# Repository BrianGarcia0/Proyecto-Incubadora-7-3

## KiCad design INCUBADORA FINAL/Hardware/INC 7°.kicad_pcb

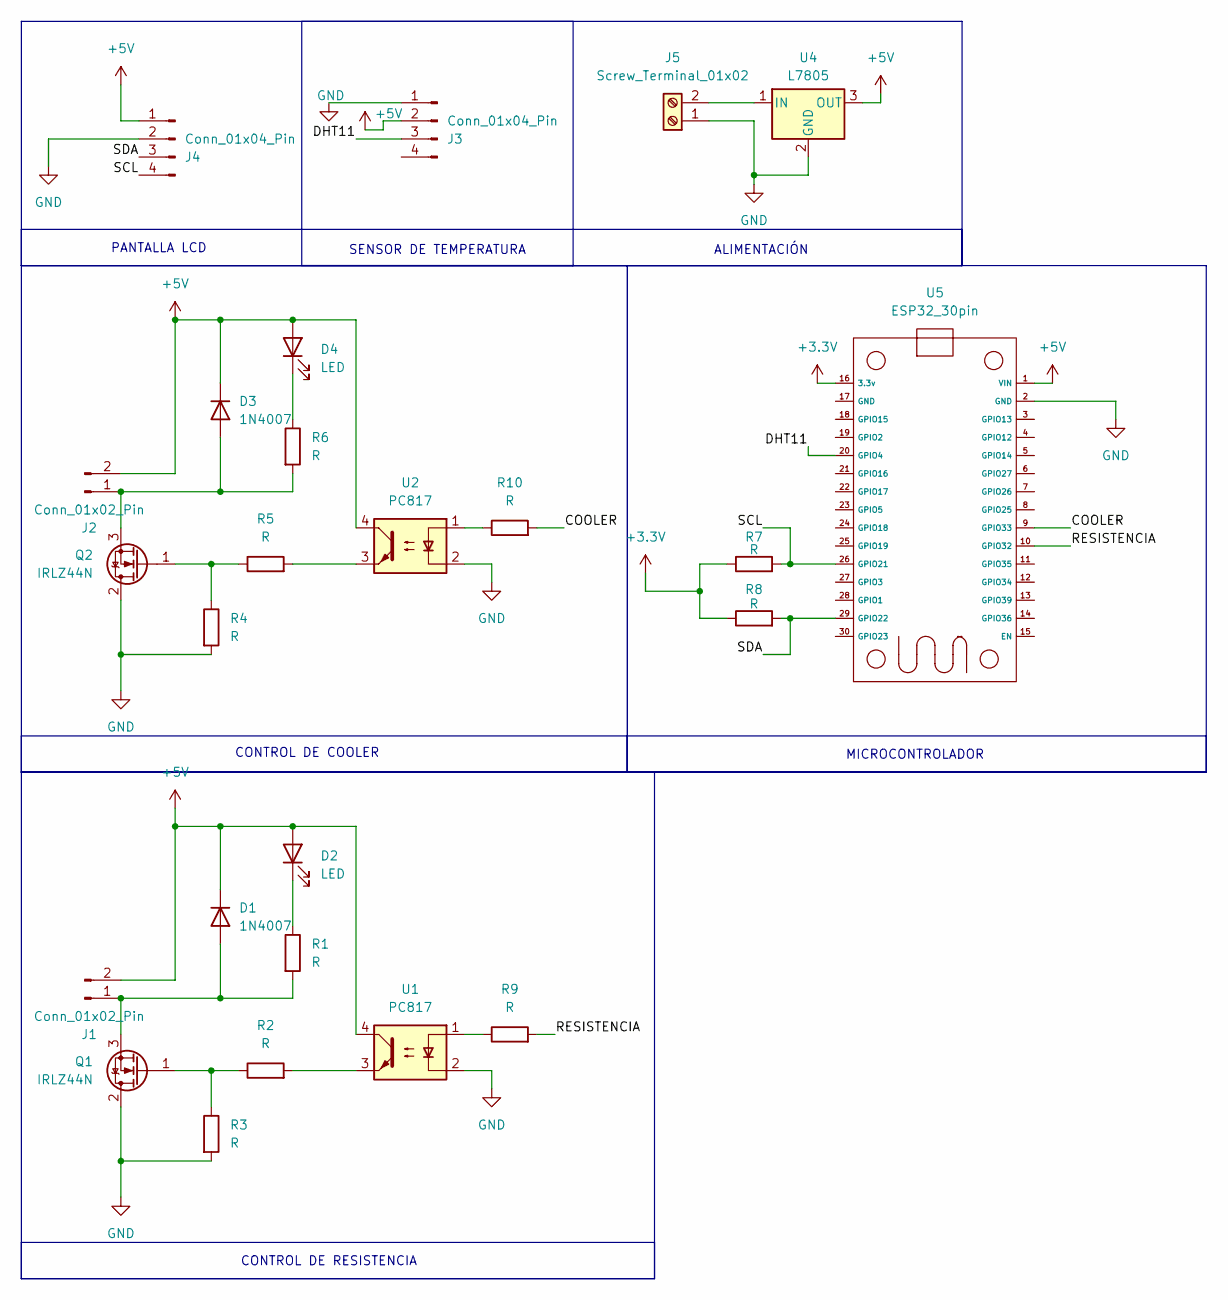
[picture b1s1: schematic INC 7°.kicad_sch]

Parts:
D1, D3: 1N4007; D_SMA
D2, D4: LED; LED_D3.0mm
J1, J2: Conn_01x02_Pin; PinSocket_1x02_P2.54mm_Vertical
J3, J4: Conn_01x04_Pin; PinSocket_1x04_P2.54mm_Vertical
J5: Screw_Terminal_01x02; TerminalBlock_MaiXu_MX126-5.0-02P_1x02_P5.00mm
Q1, Q2: IRLZ44N; TO-220-3_Vertical
R1, R2, R3, R4, R5, R6, R7, R8, R9, R10: R; R_0805_2012Metric
U1, U2: PC817; DIP-4_W7.62mm
U4: L7805; TO-220-3_Vertical
U5: ESP32_30pin

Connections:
+3.3V: R7.1, R8.1, U5.16 (3.3v)
+5V: D1.1 (K), D2.2 (A), D3.1 (K), D4.2 (A), J1.2, J2.2, J3.2, J4.1, U1.4, U2.4, U4.3 (OUT), U5.1 (VIN)
/COOLER: R10.2, U5.9 (GPIO33)
/DHT11: J3.3, U5.20 (GPIO4)
/RESISTENCIA: R9.2, U5.10 (GPIO32)
/SCL: J4.4, R7.2, U5.26 (GPIO21)
/SDA: J4.3, R8.2, U5.29 (GPIO22)
GND: J3.1, J4.2, J5.1, Q1.2 (D), Q2.2 (D), R3.2, R4.2, U1.2, U2.2, U4.2 (GND), U5.2 (GND)
unnamed: D1.2 (A), J1.1, Q1.3 (S), R1.2
unnamed: D2.1 (K), R1.1
unnamed: D3.2 (A), J2.1, Q2.3 (S), R6.2
unnamed: D4.1 (K), R6.1
unnamed: J5.2, U4.1 (IN)
unnamed: Q1.1 (G), R2.1, R3.1
unnamed: Q2.1 (G), R4.1, R5.1
unnamed: R2.2, U1.3
unnamed: R5.2, U2.3
unnamed: R9.1, U1.1
unnamed: R10.1, U2.1

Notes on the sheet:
CONTROL DE RESISTENCIA
PANTALLA LCD
MICROCONTROLADOR
CONTROL DE COOLER
SENSOR DE TEMPERATURA
ALIMENTACIÓN

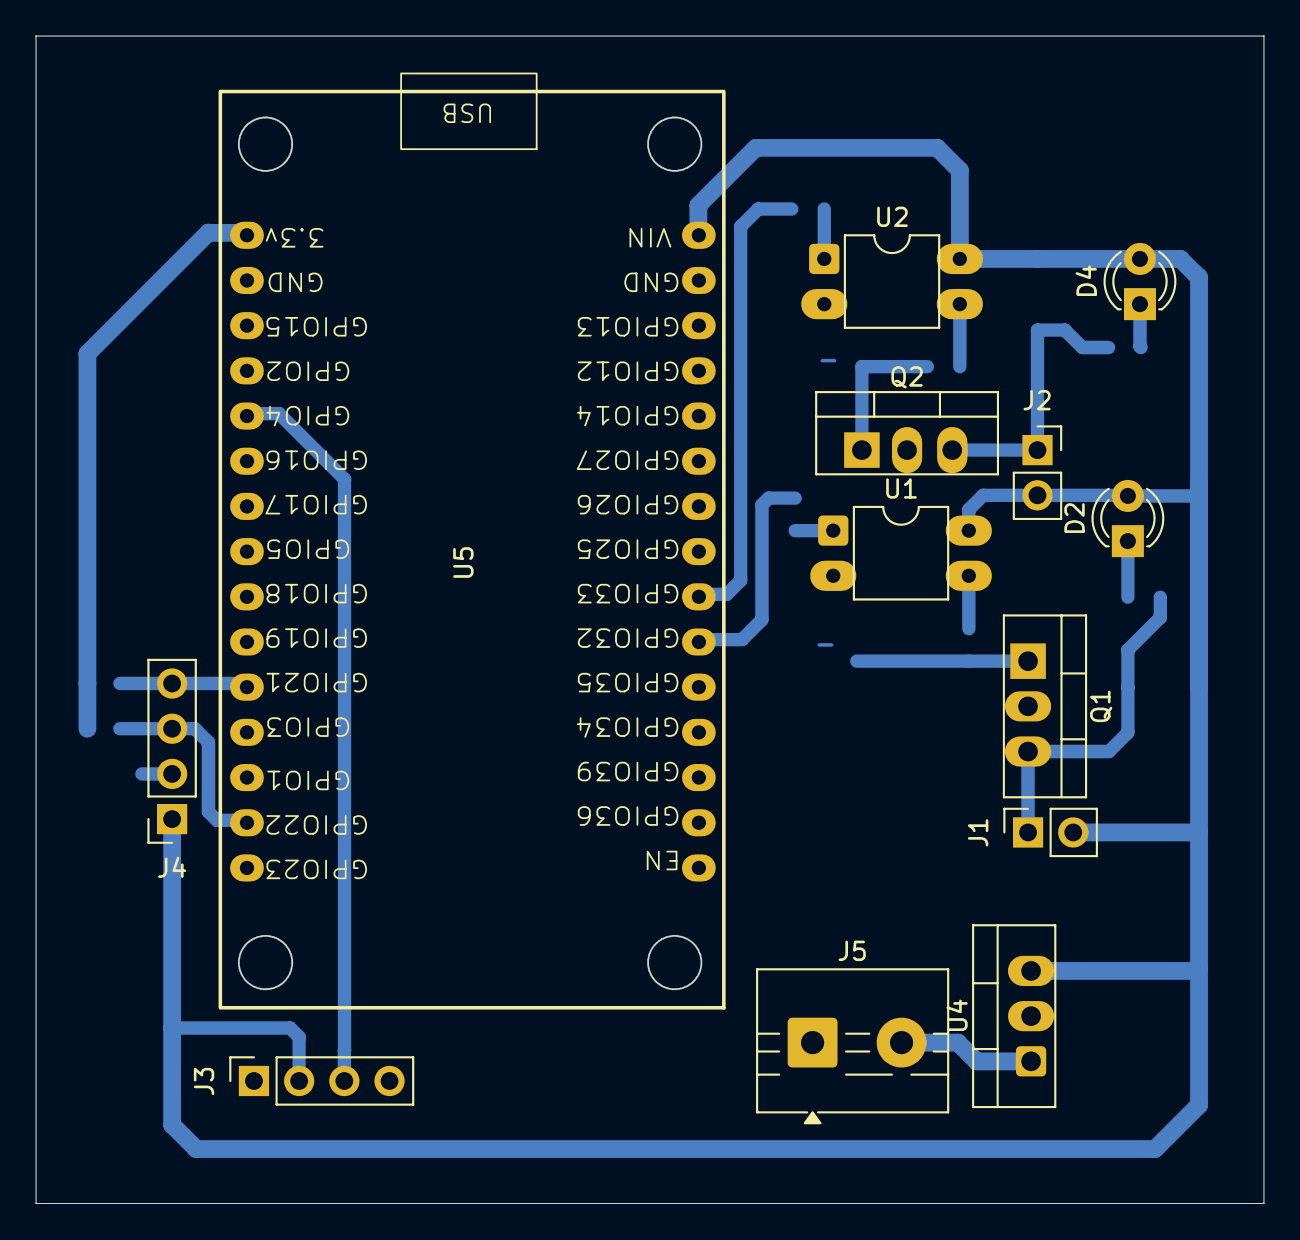
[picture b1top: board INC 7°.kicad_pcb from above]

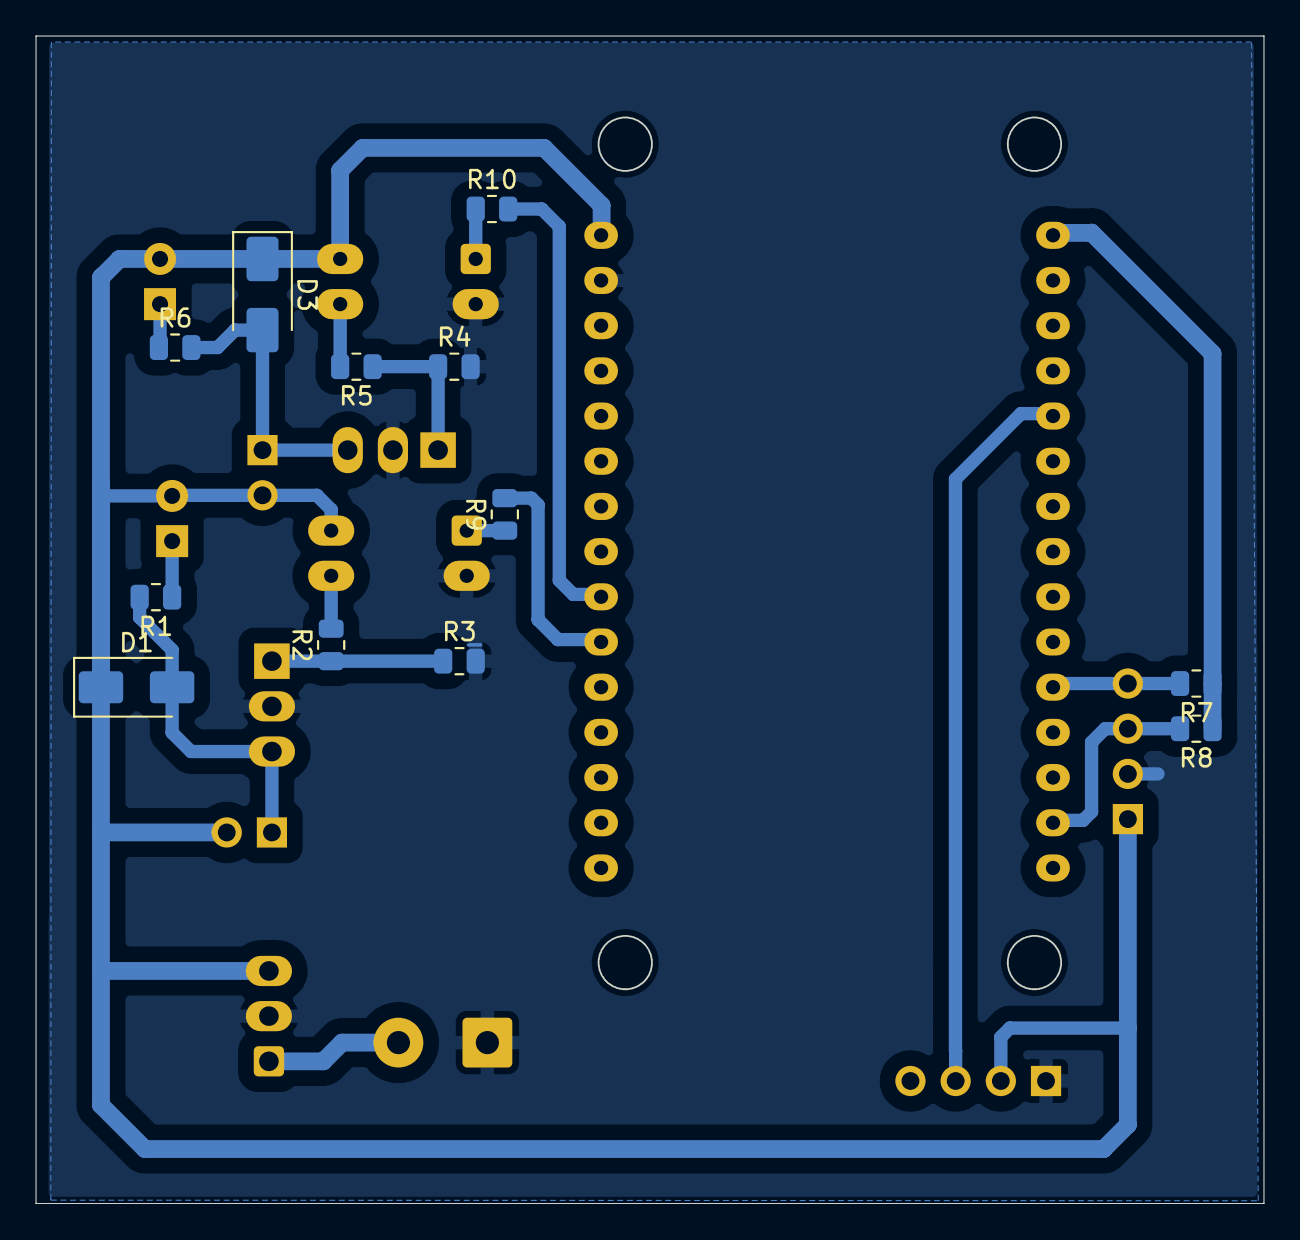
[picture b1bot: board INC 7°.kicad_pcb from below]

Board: 2 copper layers, 69.0 x 65.6 mm, 25 parts (12 on the bottom side), 19 nets.

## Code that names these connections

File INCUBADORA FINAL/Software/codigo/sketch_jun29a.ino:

#include <LiquidCrystal_I2C.h>

#include <DHT.h>
#include <Wire.h>

//====================================================
// CONFIGURACIÓN DE PINES (ESP32)
//====================================================

#define DHTPIN      4       // GPIO4
#define DHTTYPE     DHT11

#define COOLER      25      // GPIO25
#define HEATER      26      // GPIO26

//====================================================
// VARIABLES
//====================================================

int contedias = 0;

float tempdht = 0;
float humdht = 0;

// Temperaturas de trabajo
const float TEMP_MIN = 37.7;
const float TEMP_MAX = 38.0;

//====================================================
// OBJETOS
//====================================================

DHT dht(DHTPIN, DHTTYPE);
LiquidCrystal_h lcd(0x27, 16, 2);

//====================================================
// ACTUALIZAR LCD
//====================================================

void Informacion()
{
    lcd.setCursor(12,0);
    lcd.print("   ");
    lcd.setCursor(12,0);
    lcd.print(contedias);

    lcd.setCursor(2,1);
    lcd.print("     ");
    lcd.setCursor(2,1);
    lcd.print(tempdht,1);

    lcd.setCursor(11,1);
    lcd.print("     ");
    lcd.setCursor(11,1);
    lcd.print(humdht,0);
}

//====================================================
// SETUP
//====================================================

void setup()
{
    Serial.begin(115200);

    dht.begin();

    // SDA = GPIO22
    // SCL = GPIO21
    Wire.begin(22,21);

    lcd.init();
    lcd.backlight();
    lcd.clear();

    lcd.setCursor(0,0);
    lcd.print("Dias:");
    lcd.setCursor(8,0);
    lcd.print("Incub.");

    lcd.setCursor(0,1);
    lcd.print("T:");

    lcd.setCursor(9,1);
    lcd.print("H:");

    pinMode(HEATER,OUTPUT);
    pinMode(COOLER,OUTPUT);

    digitalWrite(HEATER,LOW);
    digitalWrite(COOLER,LOW);

    Serial.println("Incubadora iniciada.");
}

//====================================================
// LOOP
//====================================================

void loop()
{
    tempdht = dht.readTemperature();
    humdht = dht.readHumidity();

    if(isnan(tempdht) || isnan(humdht))
    {
        Serial.println("Error al leer DHT11");
        delay(1000);
        return;
    }

    //------------------------------------------------
    // CONTROL DE TEMPERATURA
    //------------------------------------------------

    if(tempdht < TEMP_MIN)
    {
        digitalWrite(HEATER,HIGH);
        digitalWrite(COOLER,LOW);
    }
    else if(tempdht > TEMP_MAX)
    {
        digitalWrite(HEATER,LOW);
        digitalWrite(COOLER,HIGH);
    }
    else
    {
        digitalWrite(HEATER,LOW);
        digitalWrite(COOLER,LOW);
    }

    //------------------------------------------------
    // LCD
    //------------------------------------------------

    Informacion();

    //------------------------------------------------
    // Monitor Serie
    //------------------------------------------------

    Serial.print("Temperatura: ");
    Serial.print(tempdht);
    Serial.print(" °C");

    Serial.print("    Humedad: ");
    Serial.print(humdht);
    Serial.println(" %");

    delay(1000);
}

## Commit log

2026-06-08 Create HARDWARE
